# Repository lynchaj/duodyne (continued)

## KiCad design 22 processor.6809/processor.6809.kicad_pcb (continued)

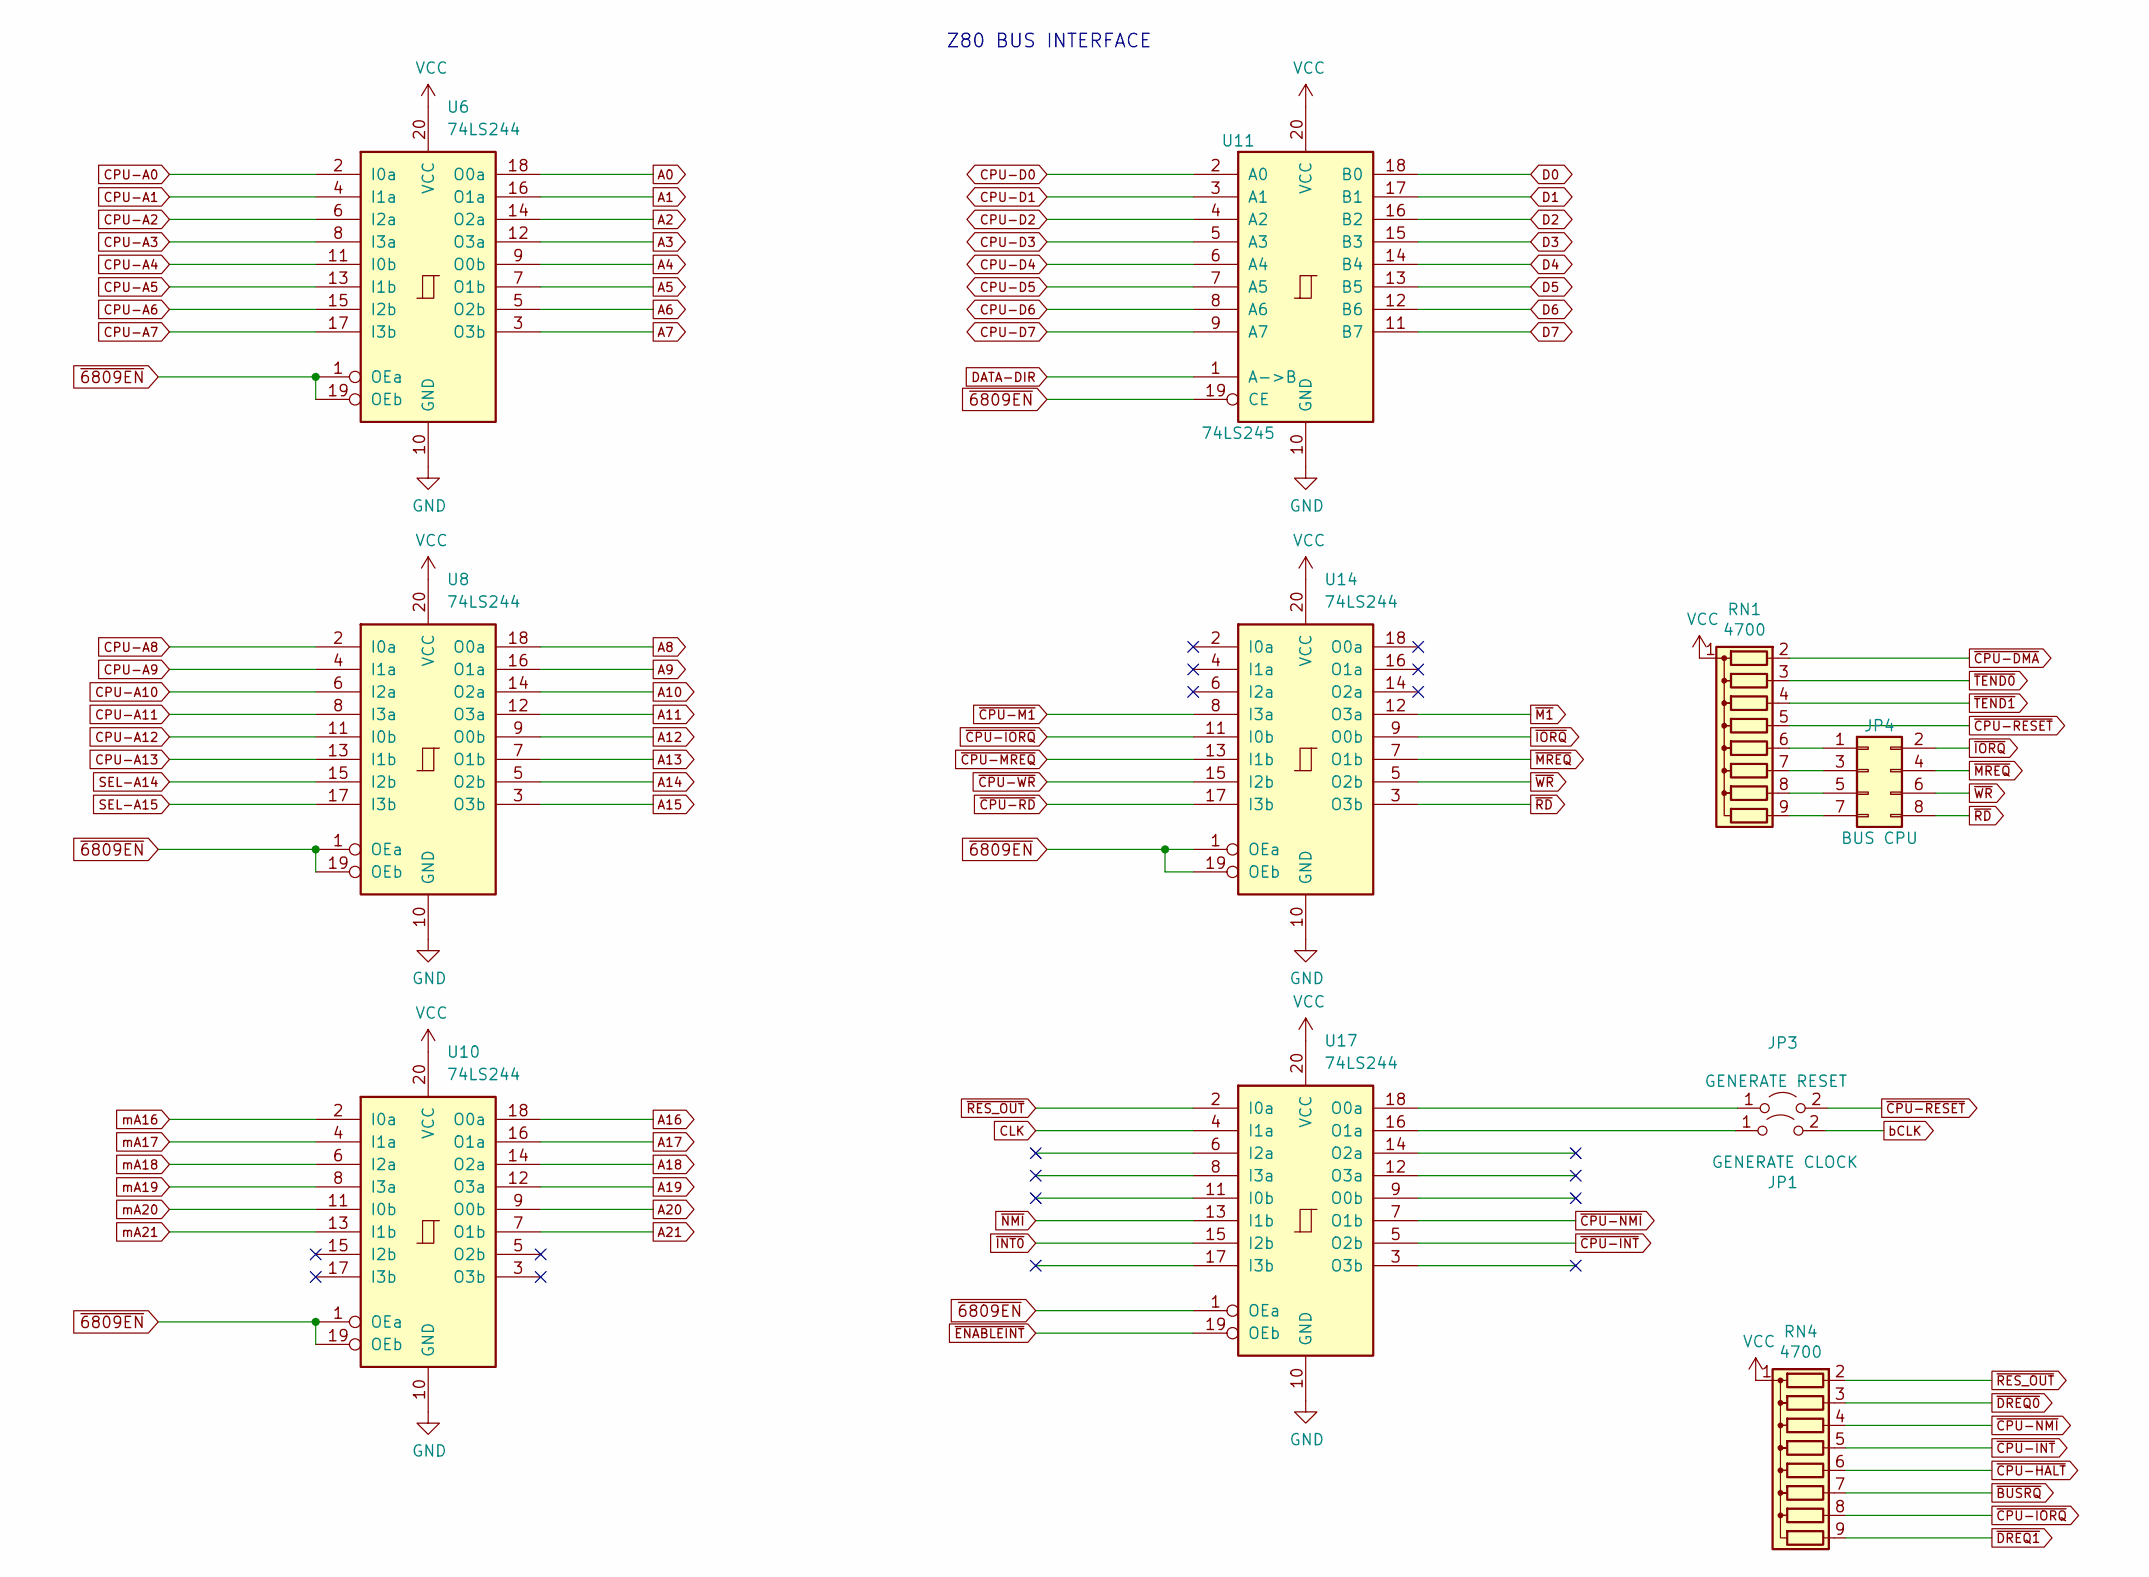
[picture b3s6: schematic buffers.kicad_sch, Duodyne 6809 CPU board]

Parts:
JP1: GENERATE CLOCK; PinHeader_1x02_P2.54mm_Vertical
JP3: GENERATE RESET; PinHeader_1x02_P2.54mm_Horizontal
JP4: BUS CPU; PinHeader_2x04_P2.54mm_Vertical
RN1, RN4: 4700; R_Array_SIP9
U6, U8, U10, U14, U17: 74LS244; DIP-20_W7.62mm_Socket_LongPads
U11: 74LS245; DIP-20_W7.62mm_Socket_LongPads

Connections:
A0: U6.18 (O0a); also elsewhere on the board
A1: U6.16 (O1a); also elsewhere on the board
A2: U6.14 (O2a); also elsewhere on the board
A3: U6.12 (O3a); also elsewhere on the board
A4: U6.9 (O0b); also elsewhere on the board
A5: U6.7 (O1b); also elsewhere on the board
A6: U6.5 (O2b); also elsewhere on the board
A7: U6.3 (O3b); also elsewhere on the board
A8: U8.18 (O0a); also elsewhere on the board
A9: U8.16 (O1a); also elsewhere on the board
A10: U8.14 (O2a); also elsewhere on the board
A11: U8.12 (O3a); also elsewhere on the board
A12: U8.9 (O0b); also elsewhere on the board
A13: U8.7 (O1b); also elsewhere on the board
A14: U8.5 (O2b); also elsewhere on the board
A15: U8.3 (O3b); also elsewhere on the board
A16: U10.18 (O0a); also elsewhere on the board
A17: U10.16 (O1a); also elsewhere on the board
A18: U10.14 (O2a); also elsewhere on the board
A19: U10.12 (O3a); also elsewhere on the board
A20: U10.9 (O0b); also elsewhere on the board
A21: U10.7 (O1b); also elsewhere on the board
CLK: U17.4 (I1a); also elsewhere on the board
CPU-A0: U6.2 (I0a); also elsewhere on the board
CPU-A1: U6.4 (I1a); also elsewhere on the board
CPU-A2: U6.6 (I2a); also elsewhere on the board
CPU-A3: U6.8 (I3a); also elsewhere on the board
CPU-A4: U6.11 (I0b); also elsewhere on the board
CPU-A5: U6.13 (I1b); also elsewhere on the board
CPU-A6: U6.15 (I2b); also elsewhere on the board
CPU-A7: U6.17 (I3b); also elsewhere on the board
CPU-A8: U8.2 (I0a); also elsewhere on the board
CPU-A9: U8.4 (I1a); also elsewhere on the board
CPU-A10: U8.6 (I2a); also elsewhere on the board
CPU-A11: U8.8 (I3a); also elsewhere on the board
CPU-A12: U8.11 (I0b); also elsewhere on the board
CPU-A13: U8.13 (I1b); also elsewhere on the board
CPU-D0: U11.2 (A0); also elsewhere on the board
CPU-D1: U11.3 (A1); also elsewhere on the board
CPU-D2: U11.4 (A2); also elsewhere on the board
CPU-D3: U11.5 (A3); also elsewhere on the board
CPU-D4: U11.6 (A4); also elsewhere on the board
CPU-D5: U11.7 (A5); also elsewhere on the board
CPU-D6: U11.8 (A6); also elsewhere on the board
CPU-D7: U11.9 (A7); also elsewhere on the board
D0: U11.18 (B0); also elsewhere on the board
D1: U11.17 (B1); also elsewhere on the board
D2: U11.16 (B2); also elsewhere on the board
D3: U11.15 (B3); also elsewhere on the board
D4: U11.14 (B4); also elsewhere on the board
D5: U11.13 (B5); also elsewhere on the board
D6: U11.12 (B6); also elsewhere on the board
D7: U11.11 (B7); also elsewhere on the board
DATA-DIR: U11.1 (A->B); also elsewhere on the board
GND: U6.10 (GND), U8.10 (GND), U10.10 (GND), U11.10 (GND), U14.10 (GND), U17.10 (GND); also elsewhere on the board
unnamed: JP1.1 (A), U17.16 (O1a)
unnamed: JP3.1 (A), U17.18 (O0a)
unnamed: JP4.1, RN1.6 (R5)
unnamed: JP4.3, RN1.7 (R6)
unnamed: JP4.5, RN1.8 (R7)
unnamed: JP4.7, RN1.9 (R8)
SEL-A14: U8.15 (I2b); also elsewhere on the board
SEL-A15: U8.17 (I3b); also elsewhere on the board
VCC: RN1.1 (common), RN4.1 (common), U6.20 (VCC), U8.20 (VCC), U10.20 (VCC), U11.20 (VCC), U14.20 (VCC), U17.20 (VCC); also elsewhere on the board
bCLK: JP1.2 (B); also elsewhere on the board
mA16: U10.2 (I0a); also elsewhere on the board
mA17: U10.4 (I1a); also elsewhere on the board
mA18: U10.6 (I2a); also elsewhere on the board
mA19: U10.8 (I3a); also elsewhere on the board
mA20: U10.11 (I0b); also elsewhere on the board
mA21: U10.13 (I1b); also elsewhere on the board
~6809EN: U6.1 (OEa), U6.19 (OEb), U8.1 (OEa), U8.19 (OEb), U10.1 (OEa), U10.19 (OEb), U11.19 (CE), U14.1 (OEa), U14.19 (OEb), U17.1 (OEa); also elsewhere on the board
~BUSRQ: RN4.7 (R6); also elsewhere on the board
~CPU-DMA: RN1.2 (R1); also elsewhere on the board
~CPU-HALT: RN4.6 (R5); also elsewhere on the board
~CPU-INT: RN4.5 (R4), U17.5 (O2b); also elsewhere on the board
~CPU-IORQ: RN4.8 (R7), U14.11 (I0b); also elsewhere on the board
~CPU-M1: U14.8 (I3a); also elsewhere on the board
~CPU-MREQ: U14.13 (I1b); also elsewhere on the board
~CPU-NMI: RN4.4 (R3), U17.7 (O1b); also elsewhere on the board
~CPU-RD: U14.17 (I3b); also elsewhere on the board
~CPU-RESET: JP3.2 (B), RN1.5 (R4); also elsewhere on the board
~CPU-WR: U14.15 (I2b); also elsewhere on the board
~DREQ0: RN4.3 (R2); also elsewhere on the board
~DREQ1: RN4.9 (R8); also elsewhere on the board
~ENABLEINT: U17.19 (OEb); also elsewhere on the board
~INT0: U17.15 (I2b); also elsewhere on the board
~IORQ: JP4.2, U14.9 (O0b); also elsewhere on the board
~M1: U14.12 (O3a); also elsewhere on the board
~MREQ: JP4.4, U14.7 (O1b); also elsewhere on the board
~NMI: U17.13 (I1b); also elsewhere on the board
~RD: JP4.8, U14.3 (O3b); also elsewhere on the board
~RES_OUT: RN4.2 (R1), U17.2 (I0a); also elsewhere on the board
~TEND0: RN1.3 (R2); also elsewhere on the board
~TEND1: RN1.4 (R3); also elsewhere on the board
~WR: JP4.6, U14.5 (O2b); also elsewhere on the board

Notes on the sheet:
Z80 BUS INTERFACE

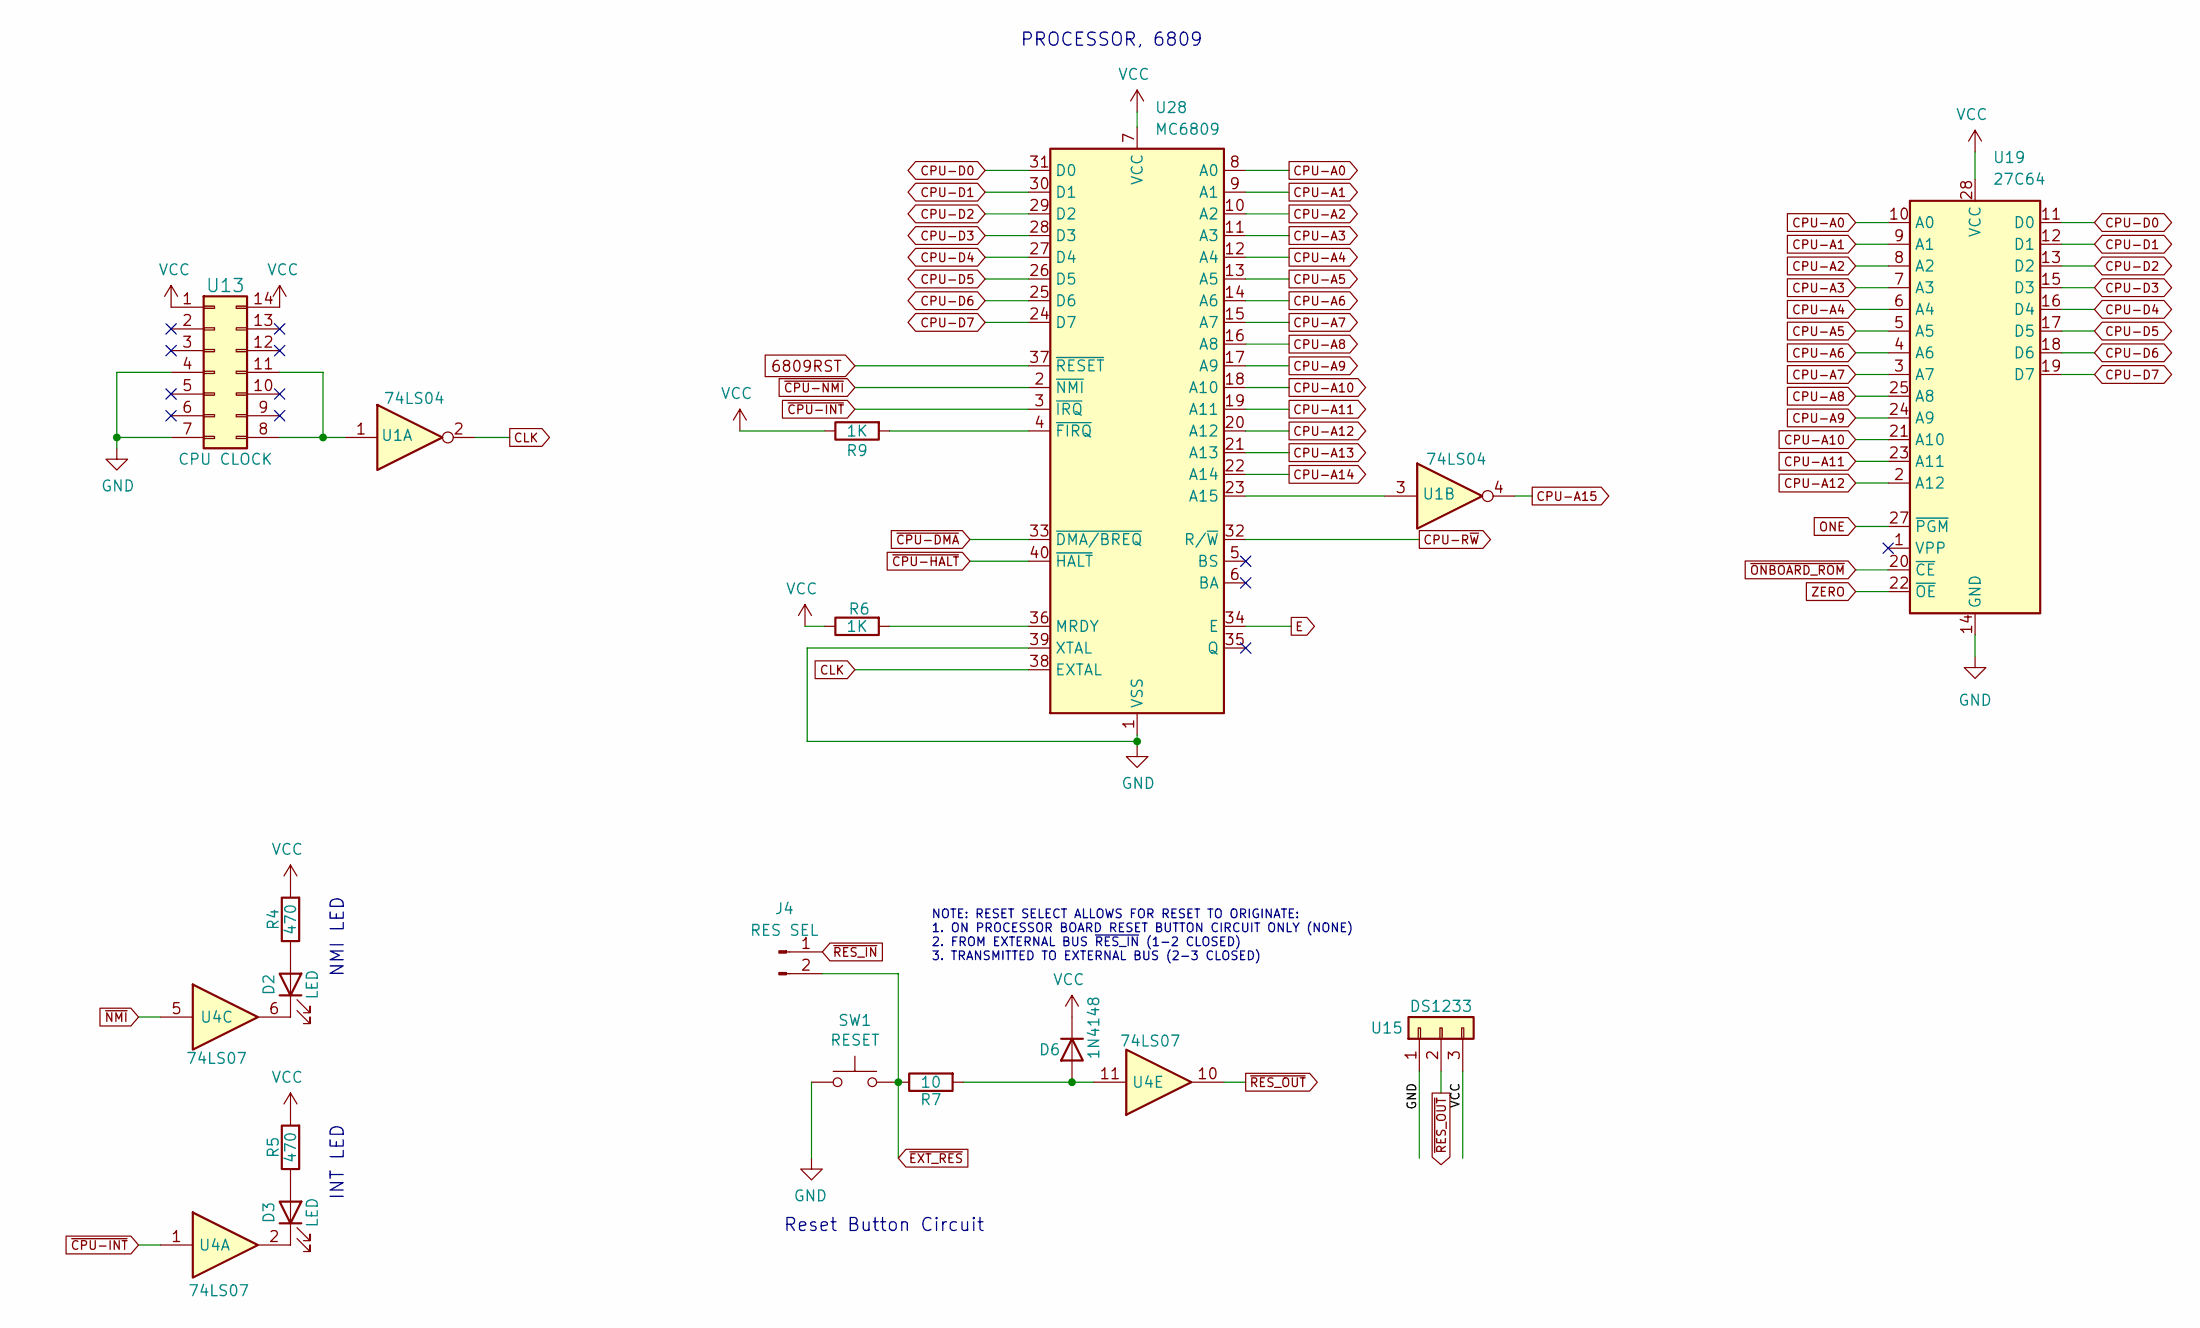
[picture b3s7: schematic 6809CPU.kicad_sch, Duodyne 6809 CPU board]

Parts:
D2, D3: LED; LED_D3.0mm_Horizontal_O3.81mm_Z2.0mm
D6: 1N4148; D_DO-35_SOD27_P7.62mm_Horizontal
J4: RES SEL; PinHeader_1x02_P2.54mm_Vertical
R4, R5: 470; R_Axial_DIN0207_L6.3mm_D2.5mm_P7.62mm_Horizontal
R6, R9: 1K; R_Axial_DIN0207_L6.3mm_D2.5mm_P7.62mm_Horizontal
R7: 10; R_Axial_DIN0207_L6.3mm_D2.5mm_P7.62mm_Horizontal
SW1: RESET; SW_Tactile_SPST_Angled_PTS645Vx58-2LFS
U1: 74LS04; DIP-14_W7.62mm_Socket_LongPads
U4: 74LS07; DIP-14_W7.62mm_Socket_LongPads
U13: CPU CLOCK; DIP-14_W7.62mm_Socket_LongPads
U15: DS1233; TO-92L_HandSolder
U19: 27C64; DIP-28_W15.24mm_Socket_LongPads
U28: MC6809; DIP-40_W15.24mm

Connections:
6809RST: U28.37 (~RESET); also elsewhere on the board
CLK: U1.2, U28.38 (EXTAL); also elsewhere on the board
CPU-A0: U19.10 (A0), U28.8 (A0); also elsewhere on the board
CPU-A1: U19.9 (A1), U28.9 (A1); also elsewhere on the board
CPU-A2: U19.8 (A2), U28.10 (A2); also elsewhere on the board
CPU-A3: U19.7 (A3), U28.11 (A3); also elsewhere on the board
CPU-A4: U19.6 (A4), U28.12 (A4); also elsewhere on the board
CPU-A5: U19.5 (A5), U28.13 (A5); also elsewhere on the board
CPU-A6: U19.4 (A6), U28.14 (A6); also elsewhere on the board
CPU-A7: U19.3 (A7), U28.15 (A7); also elsewhere on the board
CPU-A8: U19.25 (A8), U28.16 (A8); also elsewhere on the board
CPU-A9: U19.24 (A9), U28.17 (A9); also elsewhere on the board
CPU-A10: U19.21 (A10), U28.18 (A10); also elsewhere on the board
CPU-A11: U19.23 (A11), U28.19 (A11); also elsewhere on the board
CPU-A12: U19.2 (A12), U28.20 (A12); also elsewhere on the board
CPU-A13: U28.21 (A13); also elsewhere on the board
CPU-A14: U28.22 (A14); also elsewhere on the board
CPU-A15: U1.4; also elsewhere on the board
CPU-D0: U19.11 (D0), U28.31 (D0); also elsewhere on the board
CPU-D1: U19.12 (D1), U28.30 (D1); also elsewhere on the board
CPU-D2: U19.13 (D2), U28.29 (D2); also elsewhere on the board
CPU-D3: U19.15 (D3), U28.28 (D3); also elsewhere on the board
CPU-D4: U19.16 (D4), U28.27 (D4); also elsewhere on the board
CPU-D5: U19.17 (D5), U28.26 (D5); also elsewhere on the board
CPU-D6: U19.18 (D6), U28.25 (D6); also elsewhere on the board
CPU-D7: U19.19 (D7), U28.24 (D7); also elsewhere on the board
CPU-R~W: U28.32 (R/~W); also elsewhere on the board
E: U28.34 (E); also elsewhere on the board
GND: SW1.2, U13.4, U13.7, U15.1, U19.14 (GND), U28.1 (VSS), U28.39 (XTAL); also elsewhere on the board
unnamed: D2.1 (K), U4.6
unnamed: D2.2 (A), R4.1
unnamed: D3.1 (K), U4.2
unnamed: D3.2 (A), R5.1
unnamed: D6.2 (A), R7.2, U4.11
unnamed: R6.2, U28.36 (MRDY)
unnamed: R9.2, U28.4 (~FIRQ)
unnamed: U1.1, U13.8, U13.11
unnamed: U1.3, U28.23 (A15)
ONE: U19.27 (~PGM); also elsewhere on the board
VCC: D6.1 (K), R4.2, R5.2, R6.1, R9.1, U13.1, U13.14, U15.3, U19.28 (VCC), U28.7 (VCC); also elsewhere on the board
ZERO: U19.22 (~OE); also elsewhere on the board
~CPU-DMA: U28.33 (~DMA/BREQ); also elsewhere on the board
~CPU-HALT: U28.40 (~HALT); also elsewhere on the board
~CPU-INT: U4.1, U28.3 (~IRQ); also elsewhere on the board
~CPU-NMI: U28.2 (~NMI); also elsewhere on the board
~EXT_RES: J4.2, R7.1, SW1.1; also elsewhere on the board
~NMI: U4.5; also elsewhere on the board
~ONBOARD_ROM: U19.20 (~CE); also elsewhere on the board
~RES_IN: J4.1; also elsewhere on the board
~RES_OUT: U4.10, U15.2; also elsewhere on the board

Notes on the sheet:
PROCESSOR, 6809
Reset Button Circuit
NMI LED
INT LED
NOTE: RESET SELECT ALLOWS FOR RESET TO ORIGINATE: 1. ON PROCESSOR BOARD RESET BUTTON CIRCUIT ONLY (NONE) 2. FROM EXTERNAL BUS ~{RES_IN} (1-2 CLOSED) 3. TRANSMITTED TO EXTERNAL BUS (2-3 CLOSED)

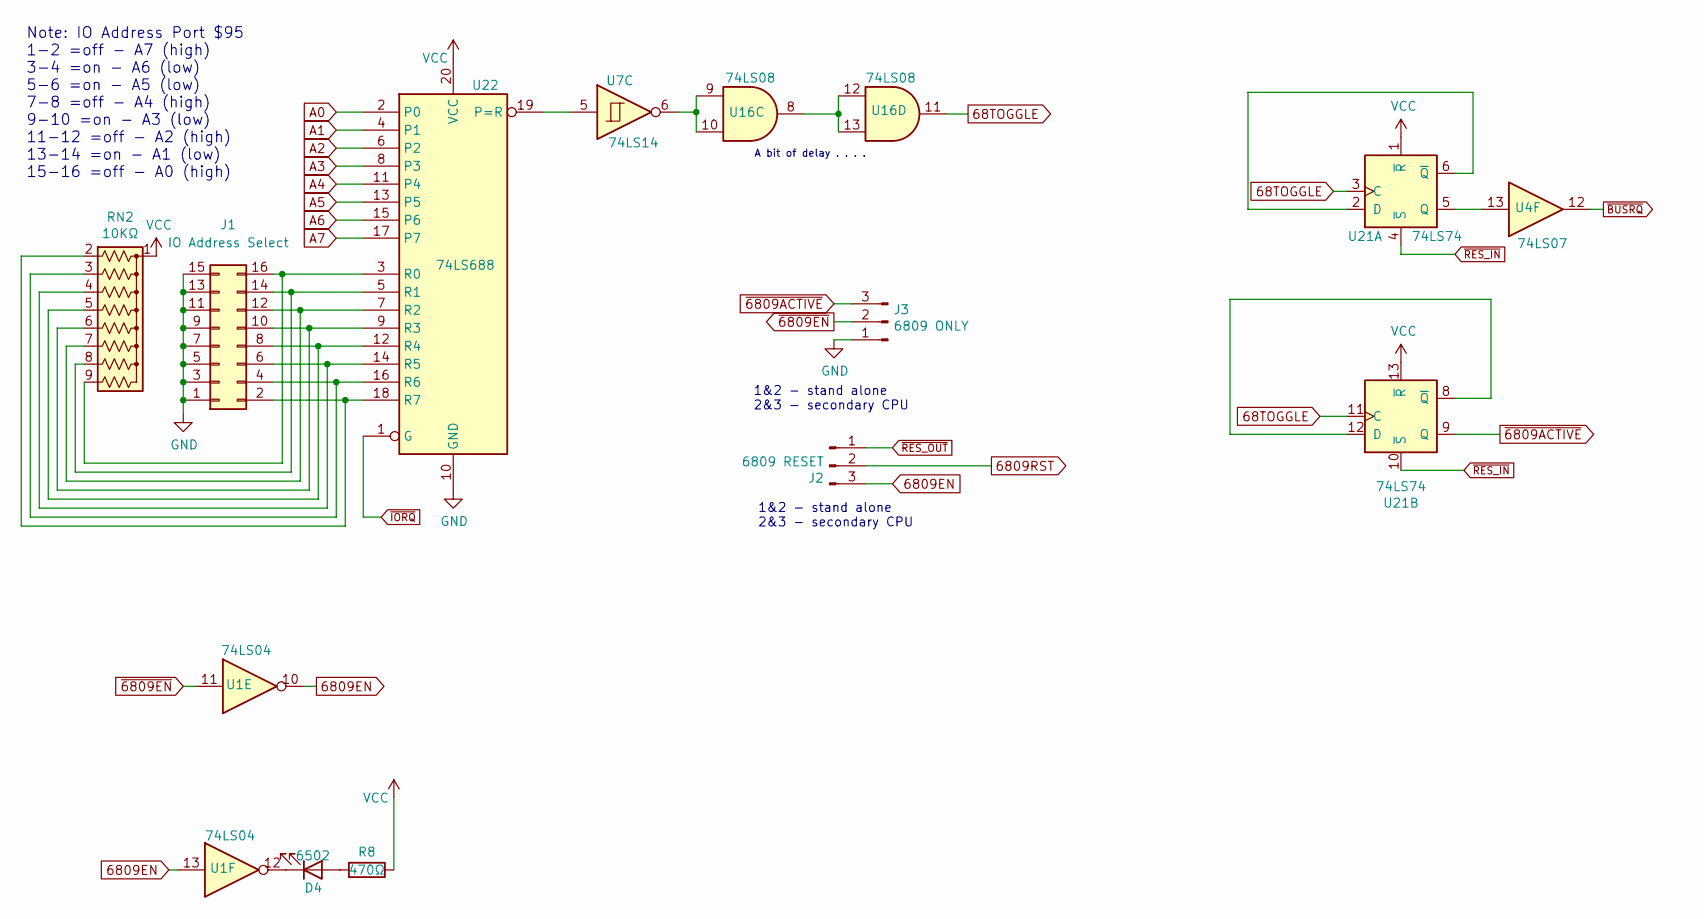
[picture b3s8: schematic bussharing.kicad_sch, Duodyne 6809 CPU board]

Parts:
D4: 6502; LED_D3.0mm_Horizontal_O3.81mm_Z2.0mm
J1: IO Address Select; PinHeader_2x08_P2.54mm_Vertical
J2: 6809 RESET; PinHeader_1x03_P2.54mm_Horizontal
J3: 6809 ONLY; PinHeader_1x03_P2.54mm_Horizontal
R8: 470Ω; R_Axial_DIN0207_L6.3mm_D2.5mm_P7.62mm_Horizontal
RN2: 10KΩ; R_Array_SIP9
U1: 74LS04; DIP-14_W7.62mm_Socket_LongPads
U4: 74LS07; DIP-14_W7.62mm_Socket_LongPads
U7: 74LS14; DIP-14_W7.62mm_Socket_LongPads
U16: 74LS08; DIP-14_W7.62mm_Socket_LongPads
U21: 74LS74; DIP-14_W7.62mm_Socket_LongPads
U22: 74LS688; DIP-20_W7.62mm_Socket_LongPads

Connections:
68TOGGLE: U16.11, U21.3 (C), U21.11 (C)
6809EN: J2.3, U1.10, U1.13
6809RST: J2.2; also elsewhere on the board
A0: U22.2 (P0); also elsewhere on the board
A1: U22.4 (P1); also elsewhere on the board
A2: U22.6 (P2); also elsewhere on the board
A3: U22.8 (P3); also elsewhere on the board
A4: U22.11 (P4); also elsewhere on the board
A5: U22.13 (P5); also elsewhere on the board
A6: U22.15 (P6); also elsewhere on the board
A7: U22.17 (P7); also elsewhere on the board
GND: J1.1, J1.3, J1.5, J1.7, J1.9, J1.11, J1.13, J1.15, J3.1, U22.10 (GND); also elsewhere on the board
unnamed: D4.1 (K), U1.12
unnamed: D4.2 (A), R8.2
unnamed: J1.2, RN2.2 (R1), U22.18 (R7)
unnamed: J1.4, RN2.3 (R2), U22.16 (R6)
unnamed: J1.6, RN2.4 (R3), U22.14 (R5)
unnamed: J1.8, RN2.5 (R4), U22.12 (R4)
unnamed: J1.10, RN2.6 (R5), U22.9 (R3)
unnamed: J1.12, RN2.7 (R6), U22.7 (R2)
unnamed: J1.14, RN2.8 (R7), U22.5 (R1)
unnamed: J1.16, RN2.9 (R8), U22.3 (R0)
unnamed: U7.6, U16.9, U16.10
unnamed: U16.8, U16.12, U16.13
unnamed: U21.2 (D), U21.6 (~Q)
unnamed: U4.13, U21.5 (Q)
unnamed: U21.8 (~Q), U21.12 (D)
unnamed: U7.5, U22.19 (P=R)
VCC: R8.1, RN2.1 (common), U21.1 (~R), U21.13 (~R), U22.20 (VCC); also elsewhere on the board
~6809ACTIVE: J3.3, U21.9 (Q)
~6809EN: J3.2, U1.11; also elsewhere on the board
~BUSRQ: U4.12; also elsewhere on the board
~IORQ: U22.1 (G); also elsewhere on the board
~RES_IN: U21.4 (~S), U21.10 (~S); also elsewhere on the board
~RES_OUT: J2.1; also elsewhere on the board

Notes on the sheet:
1&2 - stand alone 2&3 - secondary CPU
A bit of delay . . . .
Note: IO Address Port $95 1-2 =off - A7 (high) 3-4 =on - A6 (low) 5-6 =on - A5 (low) 7-8 =off - A4 (high) 9-10 =on - A3 (low) 11-12 =off - A2 (high) 13-14 =on - A1 (low) 15-16 =off - A0 (high)

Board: 2 copper layers, 111 parts (0 on the bottom side), 200 nets, no tracks yet.

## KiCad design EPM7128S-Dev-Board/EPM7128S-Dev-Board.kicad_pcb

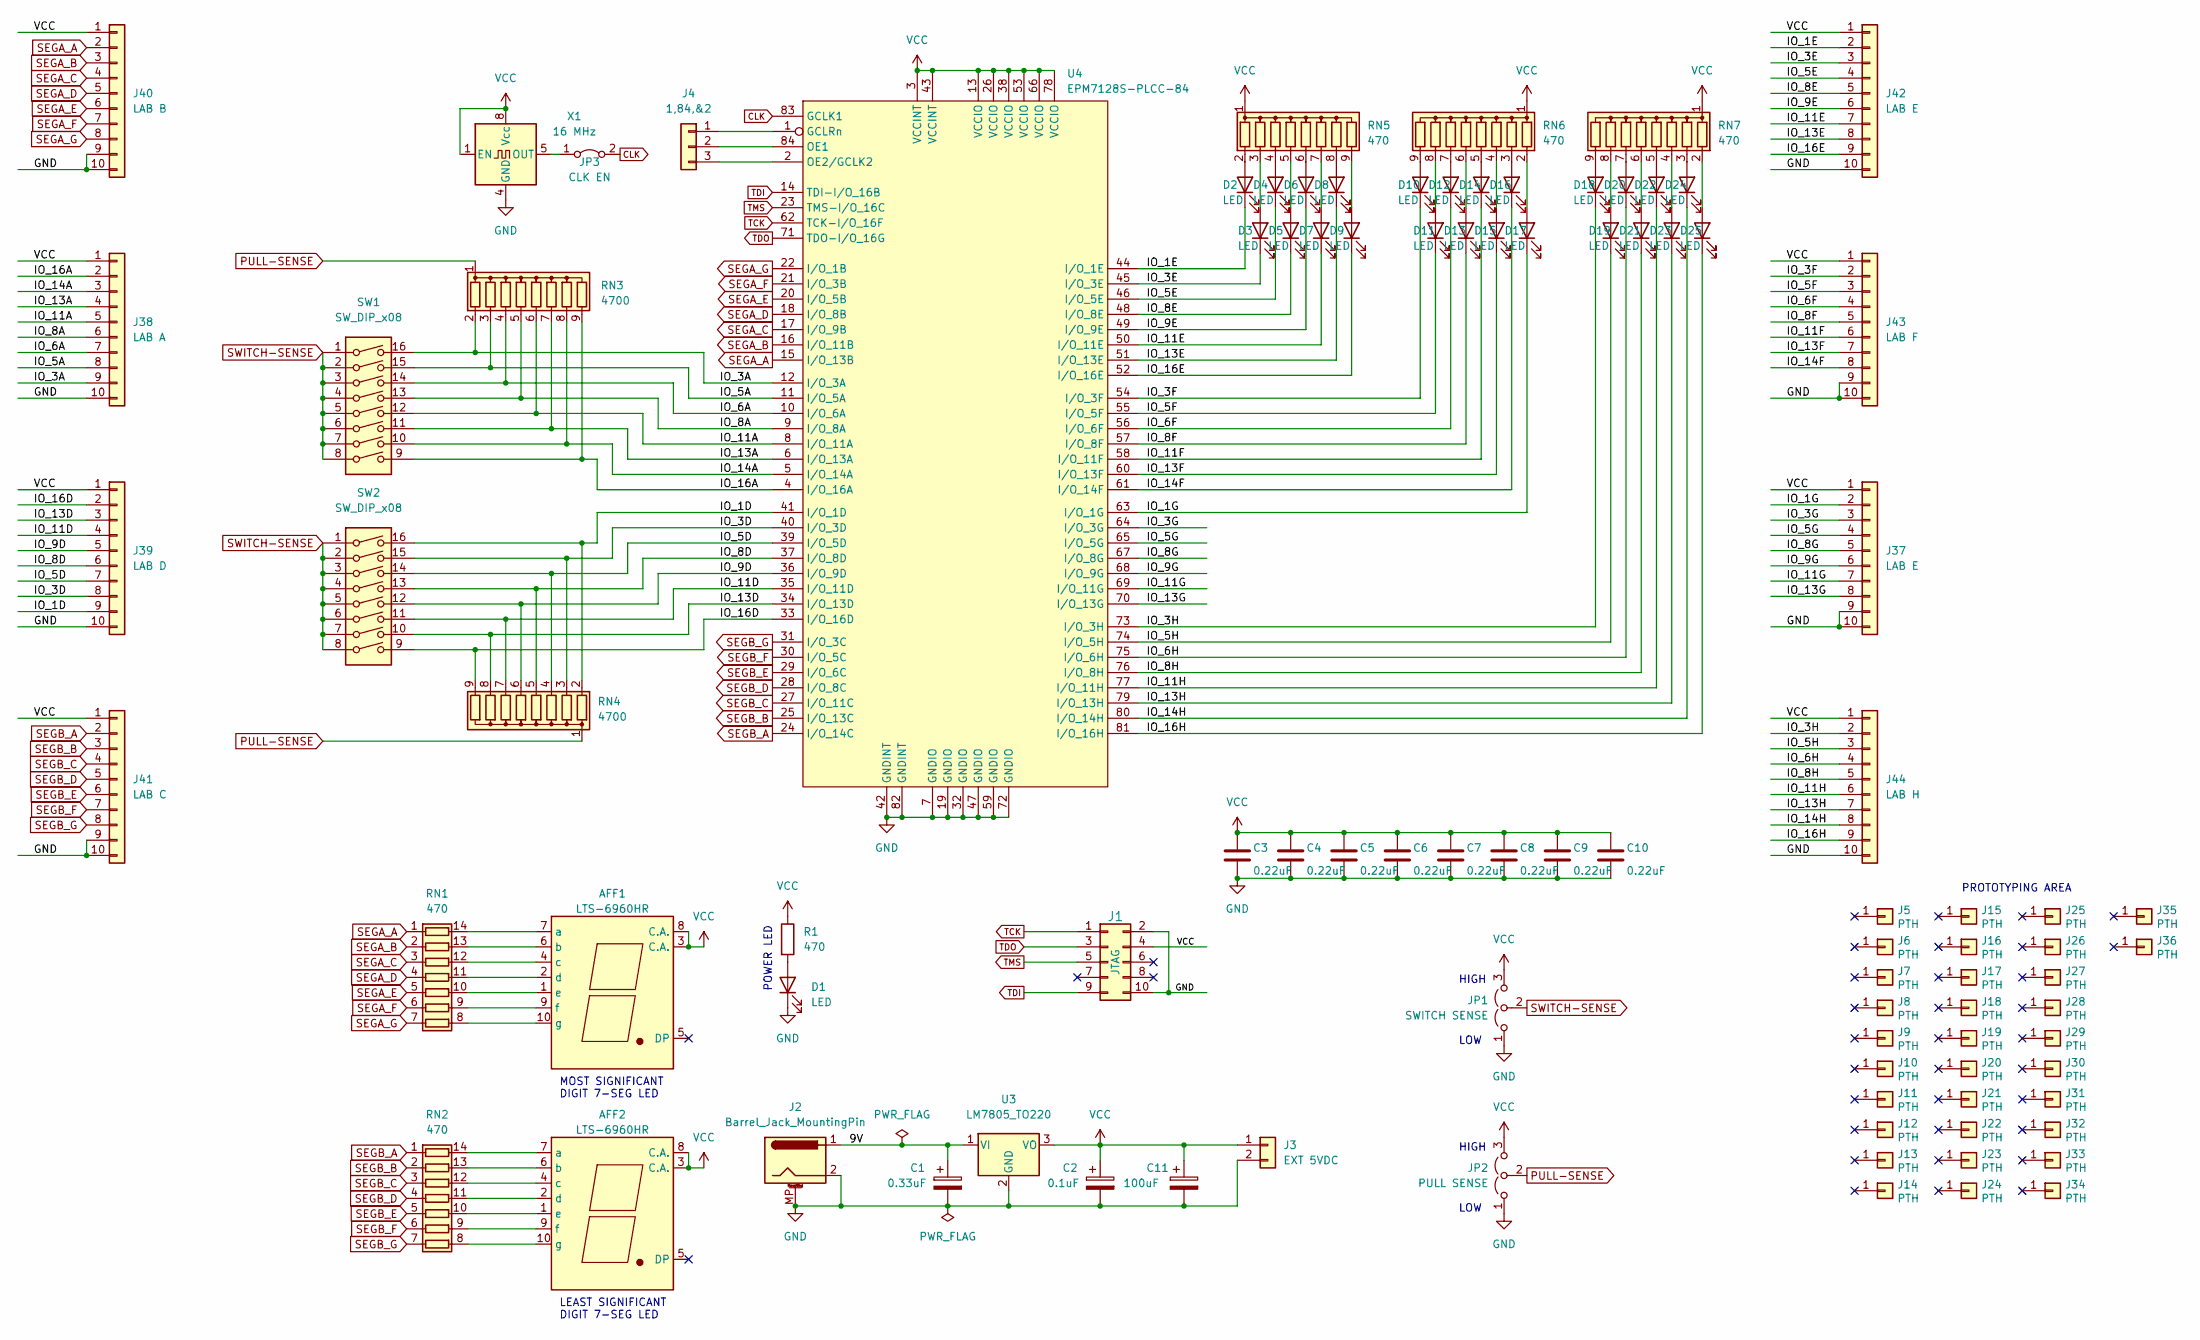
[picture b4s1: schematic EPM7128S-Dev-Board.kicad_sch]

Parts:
AFF1, AFF2: LTS-6960HR; 7SegmentLED_LTS6760_LTS6780
C1: 0.33uF; CP_Radial_D5.0mm_P2.50mm
C2: 0.1uF; C_Disc_D5.0mm_W2.5mm_P5.00mm
C3, C4, C5, C6, C7, C8, C9, C10: 0.22uF; C_Disc_D5.0mm_W2.5mm_P5.00mm
C11: 100uF; CP_Radial_D5.0mm_P2.50mm
D1, D2, D3, D4, D5, D6, D7, D8, D9, D10, D11, D12, D13, D14, D15, D16, D17, D18, D19, D20, D21, D22, D23, D24, D25: LED; LED_D3.0mm
J1: JTAG; IDC-Header_2x05_P2.54mm_Vertical
J2: Barrel_Jack_MountingPin; BarrelJack_Horizontal
J3: EXT 5VDC; PinHeader_1x02_P2.54mm_Vertical
J4: 1,84,&2; PinSocket_1x03_P2.54mm_Vertical
J5, J6, J7, J8, J9, J10, J11, J12, J13, J14, J15, J16, J17, J18, J19, J20, J21, J22, J23, J24, J25, J26, J27, J28, J29, J30, J31, J32, J33, J34, J35, J36: PTH; PTHelement
J37, J42: LAB E; PinSocket_1x10_P2.54mm_Vertical
J38: LAB A; PinSocket_1x10_P2.54mm_Vertical
J39: LAB D; PinSocket_1x10_P2.54mm_Vertical
J40: LAB B; PinSocket_1x10_P2.54mm_Vertical
J41: LAB C; PinSocket_1x10_P2.54mm_Vertical
J43: LAB F; PinSocket_1x10_P2.54mm_Vertical
J44: LAB H; PinSocket_1x10_P2.54mm_Vertical
JP1: SWITCH SENSE; PinHeader_1x03_P2.54mm_Vertical
JP2: PULL SENSE; PinHeader_1x03_P2.54mm_Vertical
JP3: CLK EN; PinHeader_1x02_P2.54mm_Vertical
R1: 470; R_Axial_DIN0207_L6.3mm_D2.5mm_P7.62mm_Horizontal
RN1, RN2: 470; DIP-14_W7.62mm
RN3, RN4: 4700; R_Array_SIP9
RN5, RN6, RN7: 470; R_Array_SIP9
SW1, SW2: SW_DIP_x08; SW_DIP_SPSTx08_Slide_9.78x22.5mm_W7.62mm_P2.54mm
U3: LM7805_TO220; TO-220-3_Vertical
U4: EPM7128S-PLCC-84; PLCC-84_THT-Socket
X1: 16 MHz; Oscillator_DIP-8

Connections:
/9V: C1.1, J2.1, U3.1 (VI)
/IO_1D: J39.9, RN4.2 (R1), SW2.16, U4.41 (I/O_1D)
/IO_1E: D2.1 (K), J42.2, U4.44 (I/O_1E)
/IO_1G: D17.1 (K), J37.2, U4.63 (I/O_1G)
/IO_3A: J38.9, RN3.2 (R1), SW1.16, U4.12 (I/O_3A)
/IO_3D: J39.8, RN4.3 (R2), SW2.15, U4.40 (I/O_3D)
/IO_3E: D3.1 (K), J42.3, U4.45 (I/O_3E)
/IO_3F: D10.1 (K), J43.2, U4.54 (I/O_3F)
/IO_3G: J37.3, U4.64 (I/O_3G)
/IO_3H: D18.1 (K), J44.2, U4.73 (I/O_3H)
/IO_5A: J38.8, RN3.3 (R2), SW1.15, U4.11 (I/O_5A)
/IO_5D: J39.7, RN4.4 (R3), SW2.14, U4.39 (I/O_5D)
/IO_5E: D4.1 (K), J42.4, U4.46 (I/O_5E)
/IO_5F: D11.1 (K), J43.3, U4.55 (I/O_5F)
/IO_5G: J37.4, U4.65 (I/O_5G)
/IO_5H: D19.1 (K), J44.3, U4.74 (I/O_5H)
/IO_6A: J38.7, RN3.4 (R3), SW1.14, U4.10 (I/O_6A)
/IO_6F: D12.1 (K), J43.4, U4.56 (I/O_6F)
/IO_6H: D20.1 (K), J44.4, U4.75 (I/O_6H)
/IO_8A: J38.6, RN3.5 (R4), SW1.13, U4.9 (I/O_8A)
/IO_8D: J39.6, RN4.5 (R4), SW2.13, U4.37 (I/O_8D)
/IO_8E: D5.1 (K), J42.5, U4.48 (I/O_8E)
/IO_8F: D13.1 (K), J43.5, U4.57 (I/O_8F)
/IO_8G: J37.5, U4.67 (I/O_8G)
/IO_8H: D21.1 (K), J44.5, U4.76 (I/O_8H)
/IO_9D: J39.5, RN4.6 (R5), SW2.12, U4.36 (I/O_9D)
/IO_9E: D6.1 (K), J42.6, U4.49 (I/O_9E)
/IO_9G: J37.6, U4.68 (I/O_9G)
/IO_11A: J38.5, RN3.6 (R5), SW1.12, U4.8 (I/O_11A)
/IO_11D: J39.4, RN4.7 (R6), SW2.11, U4.35 (I/O_11D)
/IO_11E: D7.1 (K), J42.7, U4.50 (I/O_11E)
/IO_11F: D14.1 (K), J43.6, U4.58 (I/O_11F)
/IO_11G: J37.7, U4.69 (I/O_11G)
/IO_11H: D22.1 (K), J44.6, U4.77 (I/O_11H)
/IO_13A: J38.4, RN3.7 (R6), SW1.11, U4.6 (I/O_13A)
/IO_13D: J39.3, RN4.8 (R7), SW2.10, U4.34 (I/O_13D)
/IO_13E: D8.1 (K), J42.8, U4.51 (I/O_13E)
/IO_13F: D15.1 (K), J43.7, U4.60 (I/O_13F)
/IO_13G: J37.8, U4.70 (I/O_13G)
/IO_13H: D23.1 (K), J44.7, U4.79 (I/O_13H)
/IO_14A: J38.3, RN3.8 (R7), SW1.10, U4.5 (I/O_14A)
/IO_14F: D16.1 (K), J43.8, U4.61 (I/O_14F)
/IO_14H: D24.1 (K), J44.8, U4.80 (I/O_14H)
/IO_16A: J38.2, RN3.9 (R8), SW1.9, U4.4 (I/O_16A)
/IO_16D: J39.2, RN4.9 (R8), SW2.9, U4.33 (I/O_16D)
/IO_16E: D9.1 (K), J42.9, U4.52 (I/O_16E)
/IO_16H: D25.1 (K), J44.9, U4.81 (I/O_16H)
CLK: JP3.2 (B), U4.83 (GCLK1)
GND: C1.2, C2.2, C3.2, C4.2, C5.2, C6.2, C7.2, C8.2, C9.2, C10.2, C11.2, D1.1 (K), J1.2, J1.10, J2.2, J2.MP (MountPin), J3.2, J37.9, J37.10, J38.10, J39.10, J40.9, J40.10, J41.9, J41.10, J42.10, J43.9, J43.10, J44.10, JP1.1 (A), JP2.1 (A), U3.2 (GND), U4.7 (GNDIO), U4.19 (GNDIO), U4.32 (GNDIO), U4.42 (GNDINT), U4.47 (GNDIO), U4.59 (GNDIO), U4.72 (GNDIO), U4.82 (GNDINT), X1.4 (GND)
unnamed: AFF1.1 (e), RN1.10 (R5.2)
unnamed: AFF1.2 (d), RN1.11 (R4.2)
unnamed: AFF1.4 (c), RN1.12 (R3.2)
unnamed: AFF1.6 (b), RN1.13 (R2.2)
unnamed: AFF1.7 (a), RN1.14 (R1.2)
unnamed: AFF1.9 (f), RN1.9 (R6.2)
unnamed: AFF1.10 (g), RN1.8 (R7.2)
unnamed: AFF2.1 (e), RN2.10 (R5.2)
unnamed: AFF2.2 (d), RN2.11 (R4.2)
unnamed: AFF2.4 (c), RN2.12 (R3.2)
unnamed: AFF2.6 (b), RN2.13 (R2.2)
unnamed: AFF2.7 (a), RN2.14 (R1.2)
unnamed: AFF2.9 (f), RN2.9 (R6.2)
unnamed: AFF2.10 (g), RN2.8 (R7.2)
unnamed: D1.2 (A), R1.2
unnamed: D2.2 (A), RN5.2 (R1)
unnamed: D3.2 (A), RN5.3 (R2)
unnamed: D4.2 (A), RN5.4 (R3)
unnamed: D5.2 (A), RN5.5 (R4)
unnamed: D6.2 (A), RN5.6 (R5)
unnamed: D7.2 (A), RN5.7 (R6)
unnamed: D8.2 (A), RN5.8 (R7)
unnamed: D9.2 (A), RN5.9 (R8)
unnamed: D10.2 (A), RN6.9 (R8)
unnamed: D11.2 (A), RN6.8 (R7)
unnamed: D12.2 (A), RN6.7 (R6)
unnamed: D13.2 (A), RN6.6 (R5)
unnamed: D14.2 (A), RN6.5 (R4)
unnamed: D15.2 (A), RN6.4 (R3)
unnamed: D16.2 (A), RN6.3 (R2)
unnamed: D17.2 (A), RN6.2 (R1)
unnamed: D18.2 (A), RN7.9 (R8)
unnamed: D19.2 (A), RN7.8 (R7)
unnamed: D20.2 (A), RN7.7 (R6)
unnamed: D21.2 (A), RN7.6 (R5)
unnamed: D22.2 (A), RN7.5 (R4)
unnamed: D23.2 (A), RN7.4 (R3)
unnamed: D24.2 (A), RN7.3 (R2)
unnamed: D25.2 (A), RN7.2 (R1)
unnamed: J4.1, U4.1 (GCLRn)
unnamed: J4.2, U4.84 (OE1)
unnamed: J4.3, U4.2 (OE2/GCLK2)
unnamed: JP3.1 (A), X1.5 (OUT)
PULL-SENSE: JP2.2 (C), RN3.1 (common), RN4.1 (common)
SEGA_A: J40.2, RN1.1 (R1.1), U4.15 (I/O_13B)
SEGA_B: J40.3, RN1.2 (R2.1), U4.16 (I/O_11B)
SEGA_C: J40.4, RN1.3 (R3.1), U4.17 (I/O_9B)
SEGA_D: J40.5, RN1.4 (R4.1), U4.18 (I/O_8B)
SEGA_E: J40.6, RN1.5 (R5.1), U4.20 (I/O_5B)
SEGA_F: J40.7, RN1.6 (R6.1), U4.21 (I/O_3B)
SEGA_G: J40.8, RN1.7 (R7.1), U4.22 (I/O_1B)
SEGB_A: J41.2, RN2.1 (R1.1), U4.24 (I/O_14C)
SEGB_B: J41.3, RN2.2 (R2.1), U4.25 (I/O_13C)
SEGB_C: J41.4, RN2.3 (R3.1), U4.27 (I/O_11C)
SEGB_D: J41.5, RN2.4 (R4.1), U4.28 (I/O_8C)
SEGB_E: J41.6, RN2.5 (R5.1), U4.29 (I/O_6C)
SEGB_F: J41.7, RN2.6 (R6.1), U4.30 (I/O_5C)
SEGB_G: J41.8, RN2.7 (R7.1), U4.31 (I/O_3C)
SWITCH-SENSE: JP1.2 (C), SW1.1, SW1.2, SW1.3, SW1.4, SW1.5, SW1.6, SW1.7, SW1.8, SW2.1, SW2.2, SW2.3, SW2.4, SW2.5, SW2.6, SW2.7, SW2.8
TCK: J1.1, U4.62 (TCK-I/O_16F)
TDI: J1.9, U4.14 (TDI-I/O_16B)
TDO: J1.3, U4.71 (TDO-I/O_16G)
TMS: J1.5, U4.23 (TMS-I/O_16C)
VCC: AFF1.3 (C.A.), AFF1.8 (C.A.), AFF2.3 (C.A.), AFF2.8 (C.A.), C2.1, C3.1, C4.1, C5.1, C6.1, C7.1, C8.1, C9.1, C10.1, C11.1, J1.4, J3.1, J37.1, J38.1, J39.1, J40.1, J41.1, J42.1, J43.1, J44.1, JP1.3 (B), JP2.3 (B), R1.1, RN5.1 (common), RN6.1 (common), RN7.1 (common), U3.3 (VO), U4.3 (VCCINT), U4.13 (VCCIO), U4.26 (VCCIO), U4.38 (VCCIO), U4.43 (VCCINT), U4.53 (VCCIO), U4.66 (VCCIO), U4.78 (VCCIO), X1.1 (EN), X1.8 (Vcc)

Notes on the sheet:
LOW
LEAST SIGNIFICANT DIGIT 7-SEG LED
HIGH
PROTOTYPING AREA
MOST SIGNIFICANT DIGIT 7-SEG LED
POWER LED

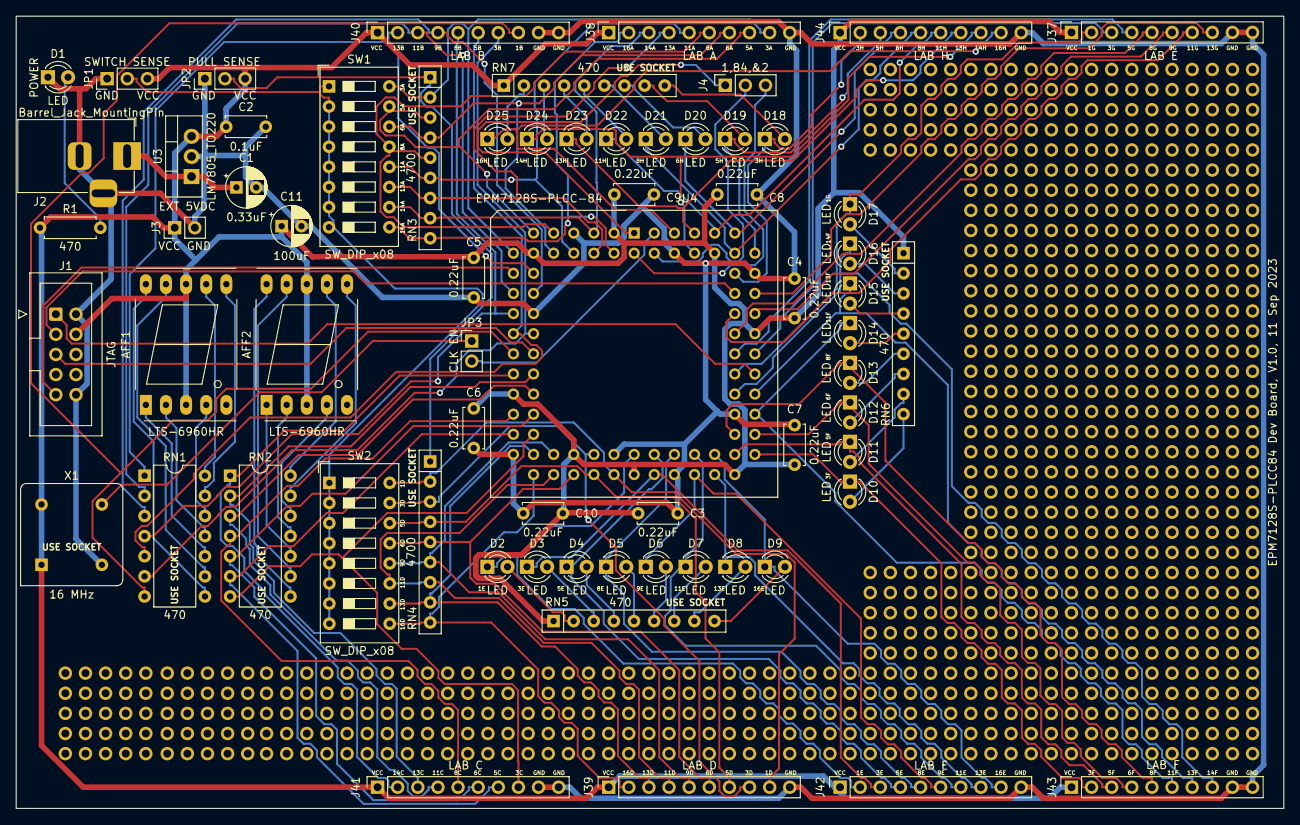
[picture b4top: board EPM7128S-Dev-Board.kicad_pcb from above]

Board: 2 copper layers, 160.0 x 100.0 mm, 98 parts (0 on the bottom side), 113 nets.
